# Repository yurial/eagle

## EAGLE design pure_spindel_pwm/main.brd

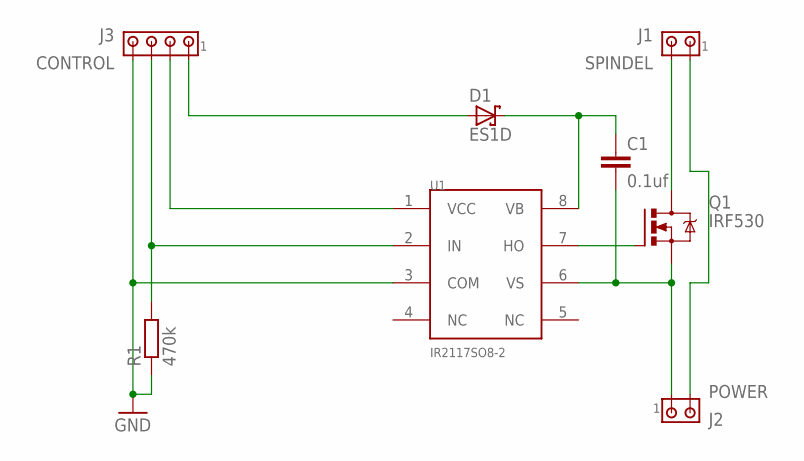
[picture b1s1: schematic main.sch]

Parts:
C1: 0.1uf; C0805K
D1: ES1D; SMB
J1: SPINDEL; 10X02MTA
J2: POWER; 10X02MTA
J3: CONTROL; 10X04MTA
Q1: IRF530; TO220BV
R1: 470k; R0603
U1: IR2117SO8-2; SO8-2

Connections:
GATE: Q1.G, U1.7 (HO)
GND: J3.4, R1.1, U1.3 (COM)
GND_48V: C1.2, J2.1, Q1.S, U1.6 (VS)
PWM: J3.3, R1.2, U1.2 (IN)
SPINDEL: J1.2, Q1.D
VB: C1.1, D1.C, U1.8 (VB)
VCC_5V: J3.2, U1.1 (VCC)
VCC_12V: D1.A, J3.1
VCC_48V: J1.1, J2.2

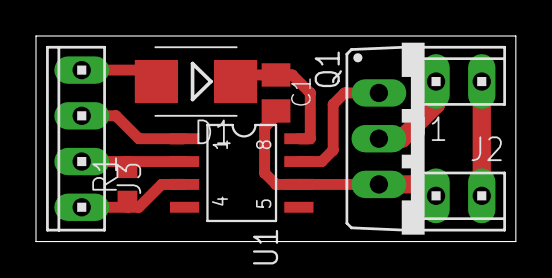
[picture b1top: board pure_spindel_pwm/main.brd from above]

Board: 2 copper layers, 26.7 x 11.4 mm, 8 parts (0 on the bottom side), 9 nets.

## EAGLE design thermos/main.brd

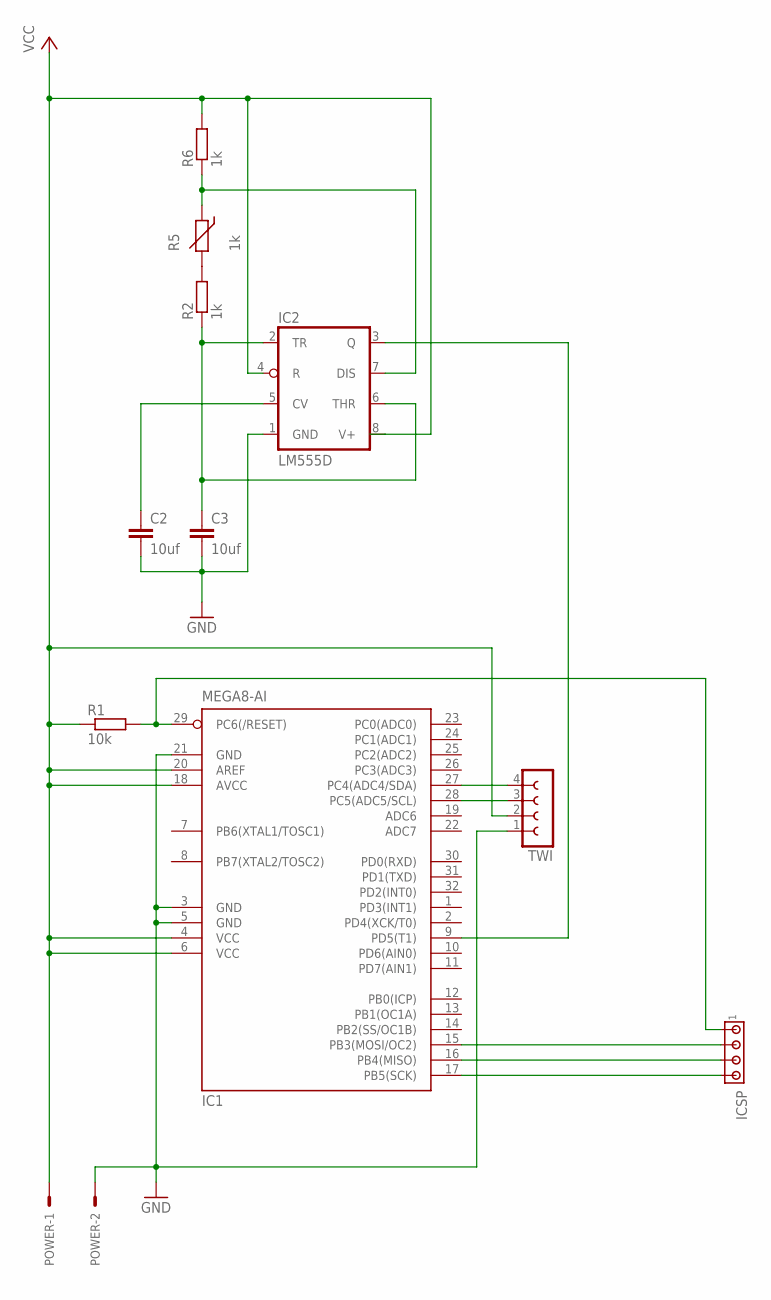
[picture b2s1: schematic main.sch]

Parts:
C2, C3: 10uf; C2012
IC1: MEGA8-AI; TQFP32-08
IC2: LM555D; SO08
ICSP: MTA04-100; 10X04MTA
POWER: 332-02
R1: 10k; 0204/7
R2, R6: 1k; M2012
R5: 1k; RS-2,5
TWI: SPB4

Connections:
GND: C2.2, C3.2, IC1.3 (GND), IC1.5 (GND), IC1.21 (GND), IC2.1 (GND), POWER.2, TWI.1
MISO: IC1.16 (PB4(MISO)), ICSP.3
MOSI: IC1.15 (PB3(MOSI/OC2)), ICSP.2
unnamed: IC1.9 (PD5(T1)), IC2.3 (Q)
unnamed: R2.2, R5.2
unnamed: C3.1, IC2.2 (TR), IC2.6 (THR), R2.1
unnamed: IC2.7 (DIS), R5.1, R6.1
unnamed: C2.1, IC2.5 (CV)
RST: IC1.29 (PC6(/RESET)), ICSP.1, R1.2
SCK: IC1.17 (PB5(SCK)), ICSP.4
SCL: IC1.28 (PC5(ADC5/SCL)), TWI.3
SDA: IC1.27 (PC4(ADC4/SDA)), TWI.4
VCC: IC1.4 (VCC), IC1.6 (VCC), IC1.18 (AVCC), IC1.20 (AREF), IC2.4 (R), IC2.8 (V+), POWER.1, R1.1, R6.2, TWI.2

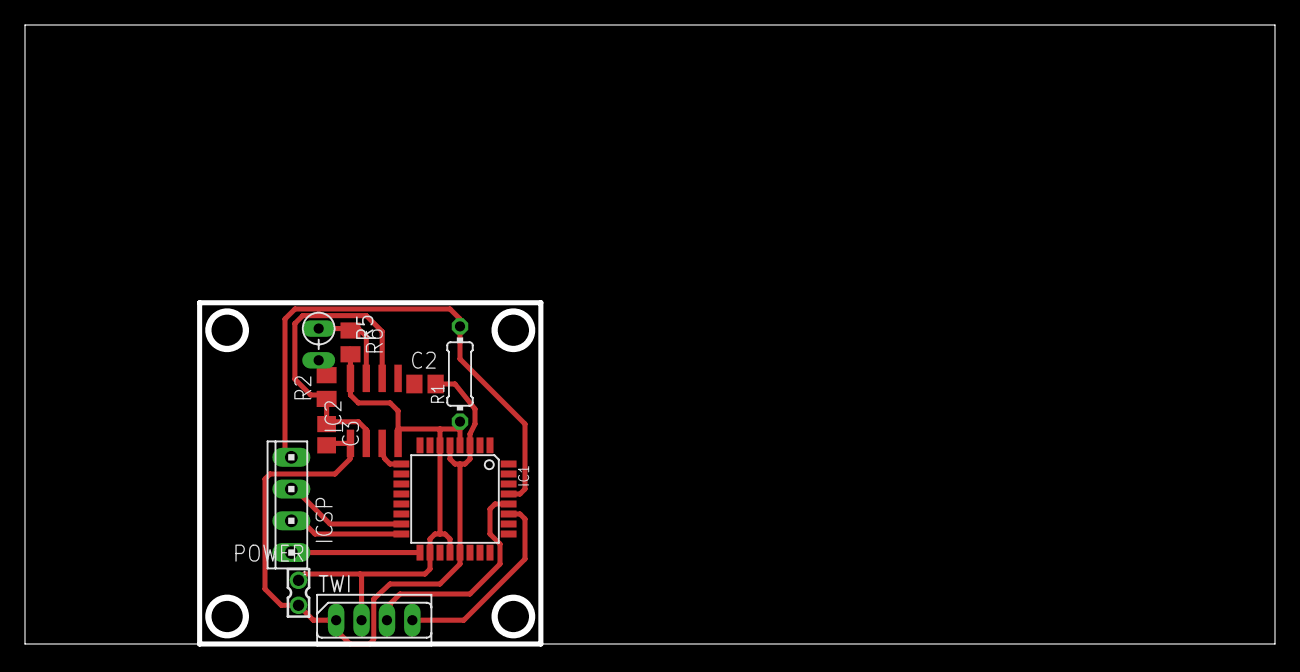
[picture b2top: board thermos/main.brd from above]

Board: 2 copper layers, 99.5 x 49.2 mm, 11 parts (0 on the bottom side), 13 nets.

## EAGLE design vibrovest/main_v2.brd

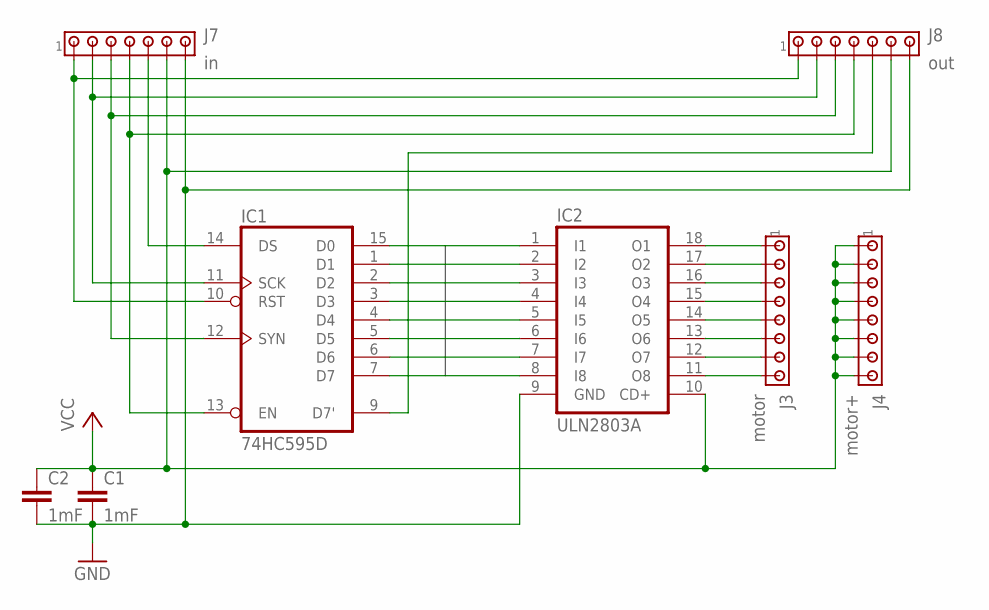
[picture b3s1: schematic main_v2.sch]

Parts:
C1: 1mF; C5B2.5
C2: 1mF; C0402
IC1: 74HC595D; SO16
IC2: ULN2803A; SO18W
J3: motor; 10X08MTA
J4: motor+; 10X08MTA
J7: in; 10X07MTA
J8: out; 10X07MTA

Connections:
D1: IC1.15 (D0), IC2.8 (I8)
D2: IC1.1 (D1), IC2.7 (I7)
D3: IC1.2 (D2), IC2.6 (I6)
D4: IC1.3 (D3), IC2.5 (I5)
D5: IC1.4 (D4), IC2.4 (I4)
D6: IC1.5 (D5), IC2.3 (I3)
D7: IC1.6 (D6), IC2.2 (I2)
D8: IC1.7 (D7), IC2.1 (I1)
GND: C1.2, C2.2, IC1.8 (GND), IC2.9 (GND), J7.7, J8.7
unnamed: IC1.13 (EN), J7.4, J8.4
unnamed: IC1.12 (SYN), J7.3, J8.3
unnamed: IC1.11 (SCK), J7.2, J8.2
unnamed: IC1.10 (RST), J7.1, J8.1
unnamed: IC1.14 (DS), J7.5
unnamed: IC1.9 (D7'), J8.5
unnamed: IC2.18 (O1), J3.1
unnamed: IC2.17 (O2), J3.2
unnamed: IC2.16 (O3), J3.3
unnamed: IC2.15 (O4), J3.4
unnamed: IC2.14 (O5), J3.5
unnamed: IC2.13 (O6), J3.6
unnamed: IC2.12 (O7), J3.7
unnamed: IC2.11 (O8), J3.8
VCC: C1.1, C2.1, IC1.16 (VCC), IC2.10 (CD+), J4.1, J4.2, J4.3, J4.4, J4.5, J4.6, J4.7, J4.8, J7.6, J8.6

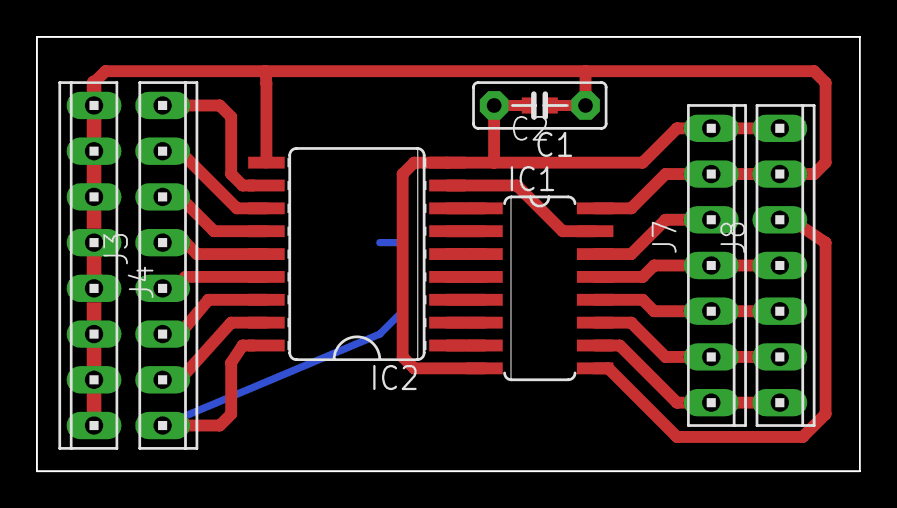
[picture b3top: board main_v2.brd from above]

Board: 2 copper layers, 45.7 x 24.1 mm, 8 parts (0 on the bottom side), 24 nets.

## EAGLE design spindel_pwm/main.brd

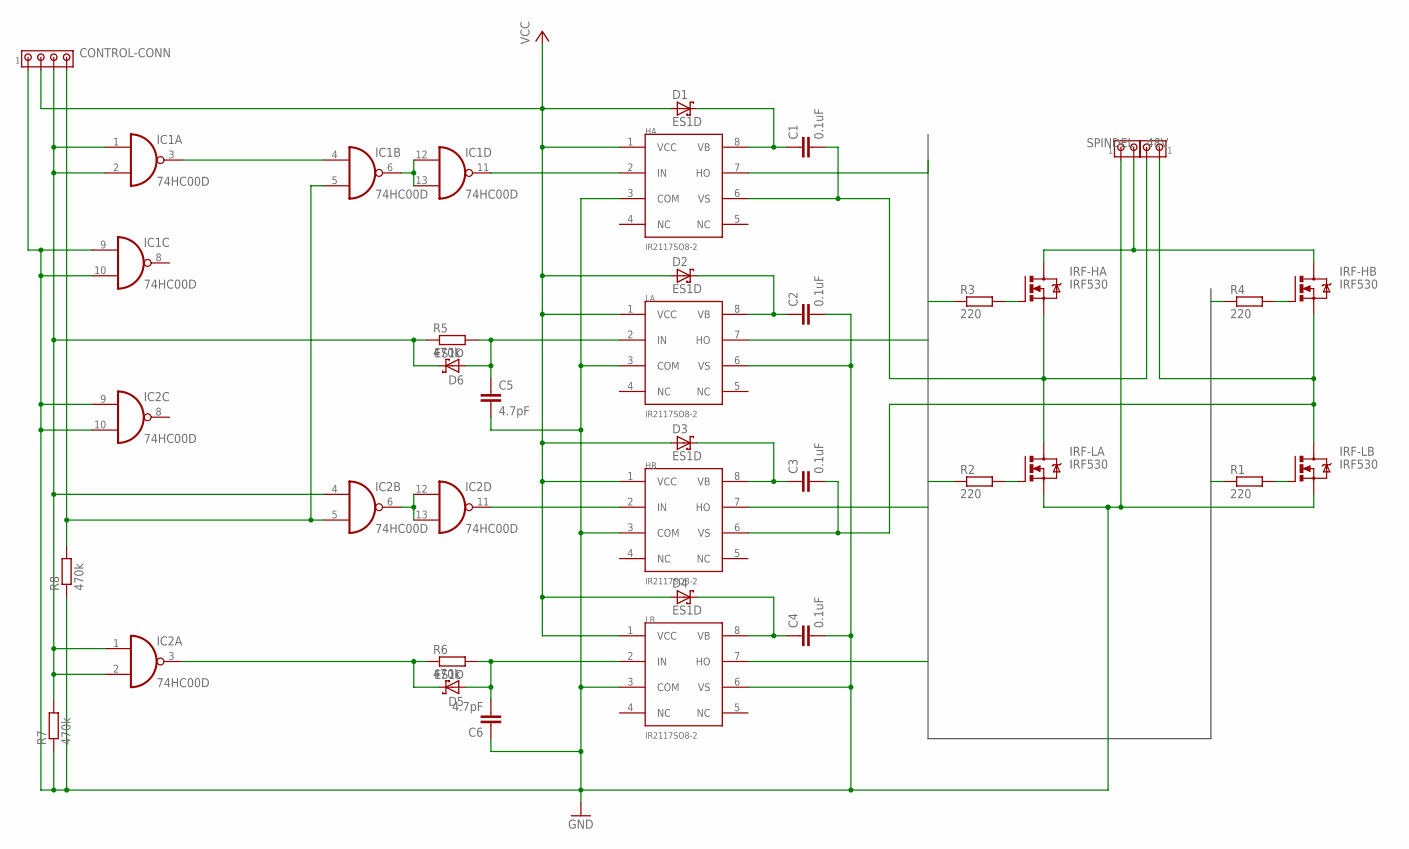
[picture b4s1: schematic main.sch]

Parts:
48V: MTA02-100; 10X02MTA
C1, C2, C3, C4: 0.1uF; C0805K
C5, C6: 4.7pF; C0805K
CONTROL-CONN: MTA04-100; 10X04MTA
D1, D2, D3, D4, D5, D6: ES1D; SMB
HA: IR2117SO8-2; SO8-2
HB: IR2117SO8-2; SO8-2
IC1, IC2: 74HC00D; SO14
IRF-HA: IRF530; TO220BV
IRF-HB: IRF530; TO220BV
IRF-LA: IRF530; TO220BV
IRF-LB: IRF530; TO220BV
LA: IR2117SO8-2; SO8-2
LB: IR2117SO8-2; SO8-2
R1, R2, R3, R4: 220; R0402
R5, R6, R7, R8: 470k; R0603
SPINDEL: MTA02-100; 10X02MTA

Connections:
48V: 48V.2, IRF-HA.D, IRF-HB.D
!DIR: D5.C, IC2.3 (O), R6.1
A-SIDE: C1.2, HA.6 (VS), IRF-HA.S, IRF-LA.D, SPINDEL.2
B-SIDE: C3.2, HB.6 (VS), IRF-HB.S, IRF-LB.D, SPINDEL.1
DIR: CONTROL-CONN.3, D6.C, IC1.1 (I0), IC1.2 (I1), IC2.1 (I0), IC2.2 (I1), IC2.4 (I0), R5.1, R7.2
GND: 48V.1, C2.2, C4.2, C5.2, C6.1, CONTROL-CONN.1, HA.3 (COM), HB.3 (COM), IC1.7 (GND), IC1.9 (I0), IC1.10 (I1), IC2.7 (GND), IC2.9 (I0), IC2.10 (I1), IRF-LA.S, IRF-LB.S, LA.3 (COM), LA.6 (VS), LB.3 (COM), LB.6 (VS), R7.1, R8.1
HA: HA.7 (HO), R3.1
HA-VB: C1.1, D1.C, HA.8 (VB)
HB: HB.7 (HO), R4.1
HB-VB: C3.1, D3.C, HB.8 (VB)
LA: LA.7 (HO), R2.1
LA-VB: C2.1, D2.C, LA.8 (VB)
LB: LB.7 (HO), R1.1
LB-VB: C4.1, D4.C, LB.8 (VB)
unnamed: C5.1, D6.A, LA.2 (IN), R5.2
unnamed: HA.2 (IN), IC1.11 (O)
unnamed: C6.2, D5.A, LB.2 (IN), R6.2
unnamed: IRF-HA.G, R3.2
unnamed: IRF-LA.G, R2.2
unnamed: IRF-HB.G, R4.2
unnamed: IRF-LB.G, R1.2
unnamed: IC2.6 (O), IC2.12 (I0), IC2.13 (I1)
unnamed: IC1.6 (O), IC1.12 (I0), IC1.13 (I1)
unnamed: HB.2 (IN), IC2.11 (O)
unnamed: IC1.3 (O), IC1.4 (I0)
PWM: CONTROL-CONN.4, IC1.5 (I1), IC2.5 (I1), R8.2
VCC: CONTROL-CONN.2, D1.A, D2.A, D3.A, D4.A, HA.1 (VCC), HB.1 (VCC), IC1.14 (VCC), IC2.14 (VCC), LA.1 (VCC), LB.1 (VCC)

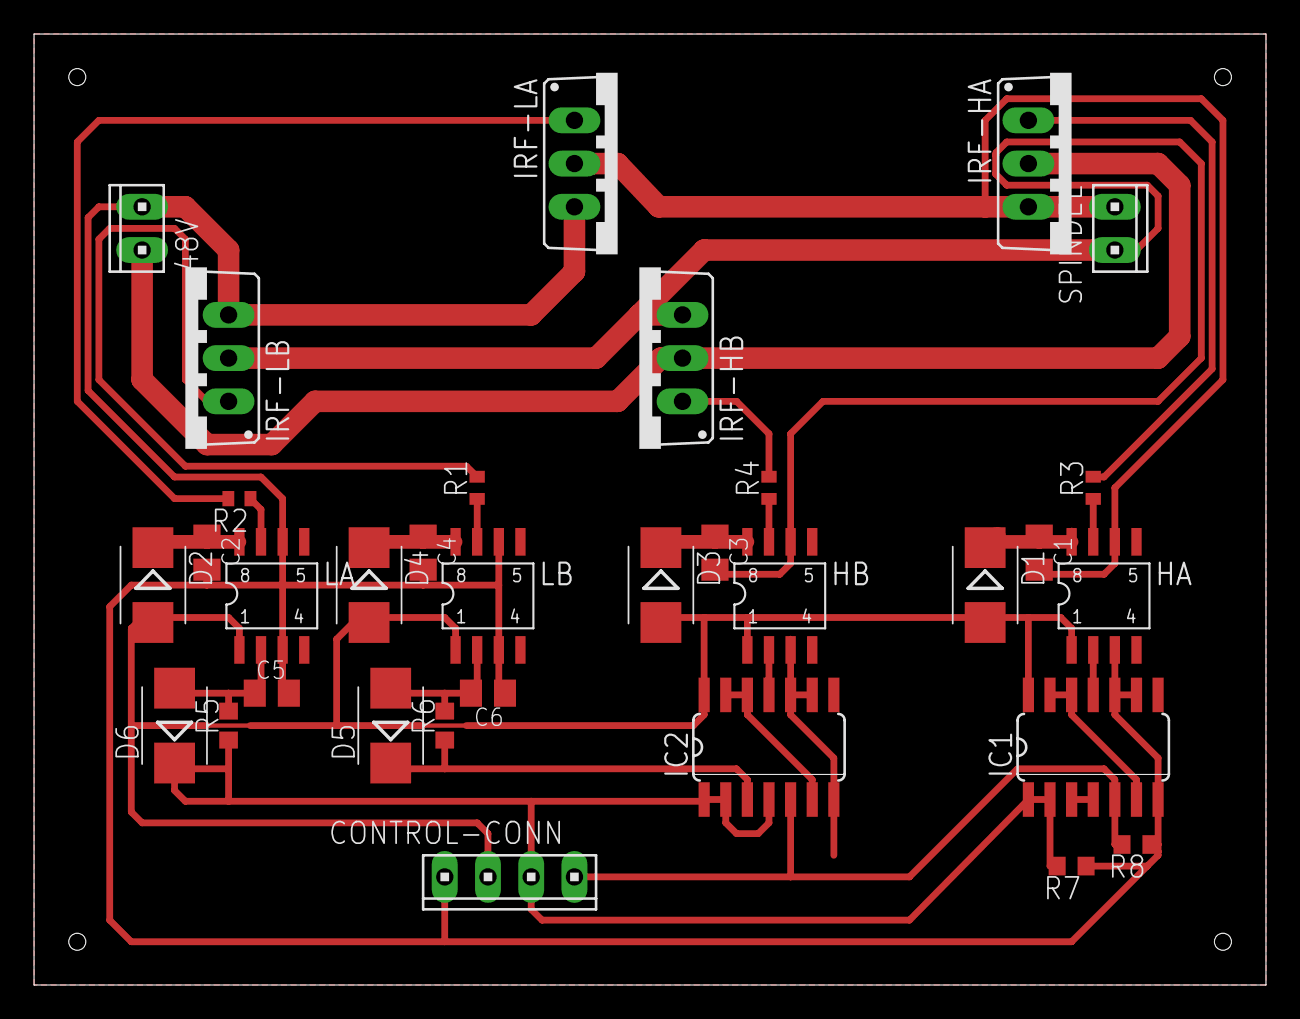
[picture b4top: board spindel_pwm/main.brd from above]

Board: 2 copper layers, 72.4 x 55.9 mm, 33 parts (0 on the bottom side), 27 nets.

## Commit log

2018-03-09 add spindel_pwm
2018-04-12 add projects: thermos, vibrovest
2018-05-02 add pure_spindel_pwm
2018-05-03 pure_spindel_pwm: fix: invalid capacitor nets

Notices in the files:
parts and their libraries:
irf-2: Copyright & License
This library is licensed under the General Public License, Version 2.
More Information about the General Public License is available at http://www.gnu.org/copyleft/gpl.html.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
